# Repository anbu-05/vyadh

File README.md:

# Team Vyadh

This repo consists of all my contributions to Team Vyadh.

## controller

### hardware and code

the controller went through many iterations. 

I had started off working with [NRF24L01](https://github.com/boneman420/vyadh/tree/master/controller/controller%20code/failed%20versions/older%20nrf%20versions) modules for wireless communication. but I could never get two nrf modules to work reliably. even when they did work the range was very bad.

there was a brief moment when i worked with [HC12](https://github.com/boneman420/vyadh/tree/master/controller/controller%20code/failed%20versions/%23hc12%2Besp_now) modules. getting these modules to work was fairly straight forward, but the range, again was not any better.

after both these modules, i decided to try out [LoRa](https://github.com/boneman420/vyadh/tree/master/controller/controller%20code/current%20versions/LoRa%20versions) (specifically the SX1278 module) -and it has been extremely reliable till now. i haven't faced any hiccups with operating the modules nor their range (i get ranges upto 1km with LOS). 

in the LoRa version, ive gone through implementing many features. the electrical subsystem itself consists of 4 main control PCBs as of now (it will be changed out soon) -the [controller](https://github.com/boneman420/vyadh/blob/master/controller/controller%20code/current%20versions/LoRa%20versions/controller_v2_duplex/controller_v2_duplex.ino) (transmitter), [reciever and traversal](https://github.com/boneman420/vyadh/blob/master/controller/controller%20code/current%20versions/LoRa%20versions/traversal_and_reciever_v3_uart_v3_duplex/traversal_and_reciever_v3_uart_v3_duplex.ino), the [robotic arm](https://github.com/boneman420/vyadh/blob/master/controller/controller%20code/current%20versions/LoRa%20versions/robotic_arm_v3_uart_v5/robotic_arm_v3_uart_v5.ino) and [the science kit](https://github.com/boneman420/vyadh/blob/master/controller/controller%20code/current%20versions/LoRa%20versions/science_kit_uart_v2/science_kit_uart_v2.ino) 

.

the controller transmits data, the reciever and traversal board recieves this data, controls the traversal and transmits the same data to the robotic arm and science kit PCBs. 

(i have also implemented duplex communication where the rover sends back telemetry data)

for the communication between these networks the initial plan was to use ESPNow. i tried it out but it creates too much lag between control and robotic arm. so we decided to just use simple serial (UART) connections for now. the future plan is to use a can BUS

### controller PCB

i also wanted to design a decided PCB for the controller. after practicing making an xl4016 buck converter

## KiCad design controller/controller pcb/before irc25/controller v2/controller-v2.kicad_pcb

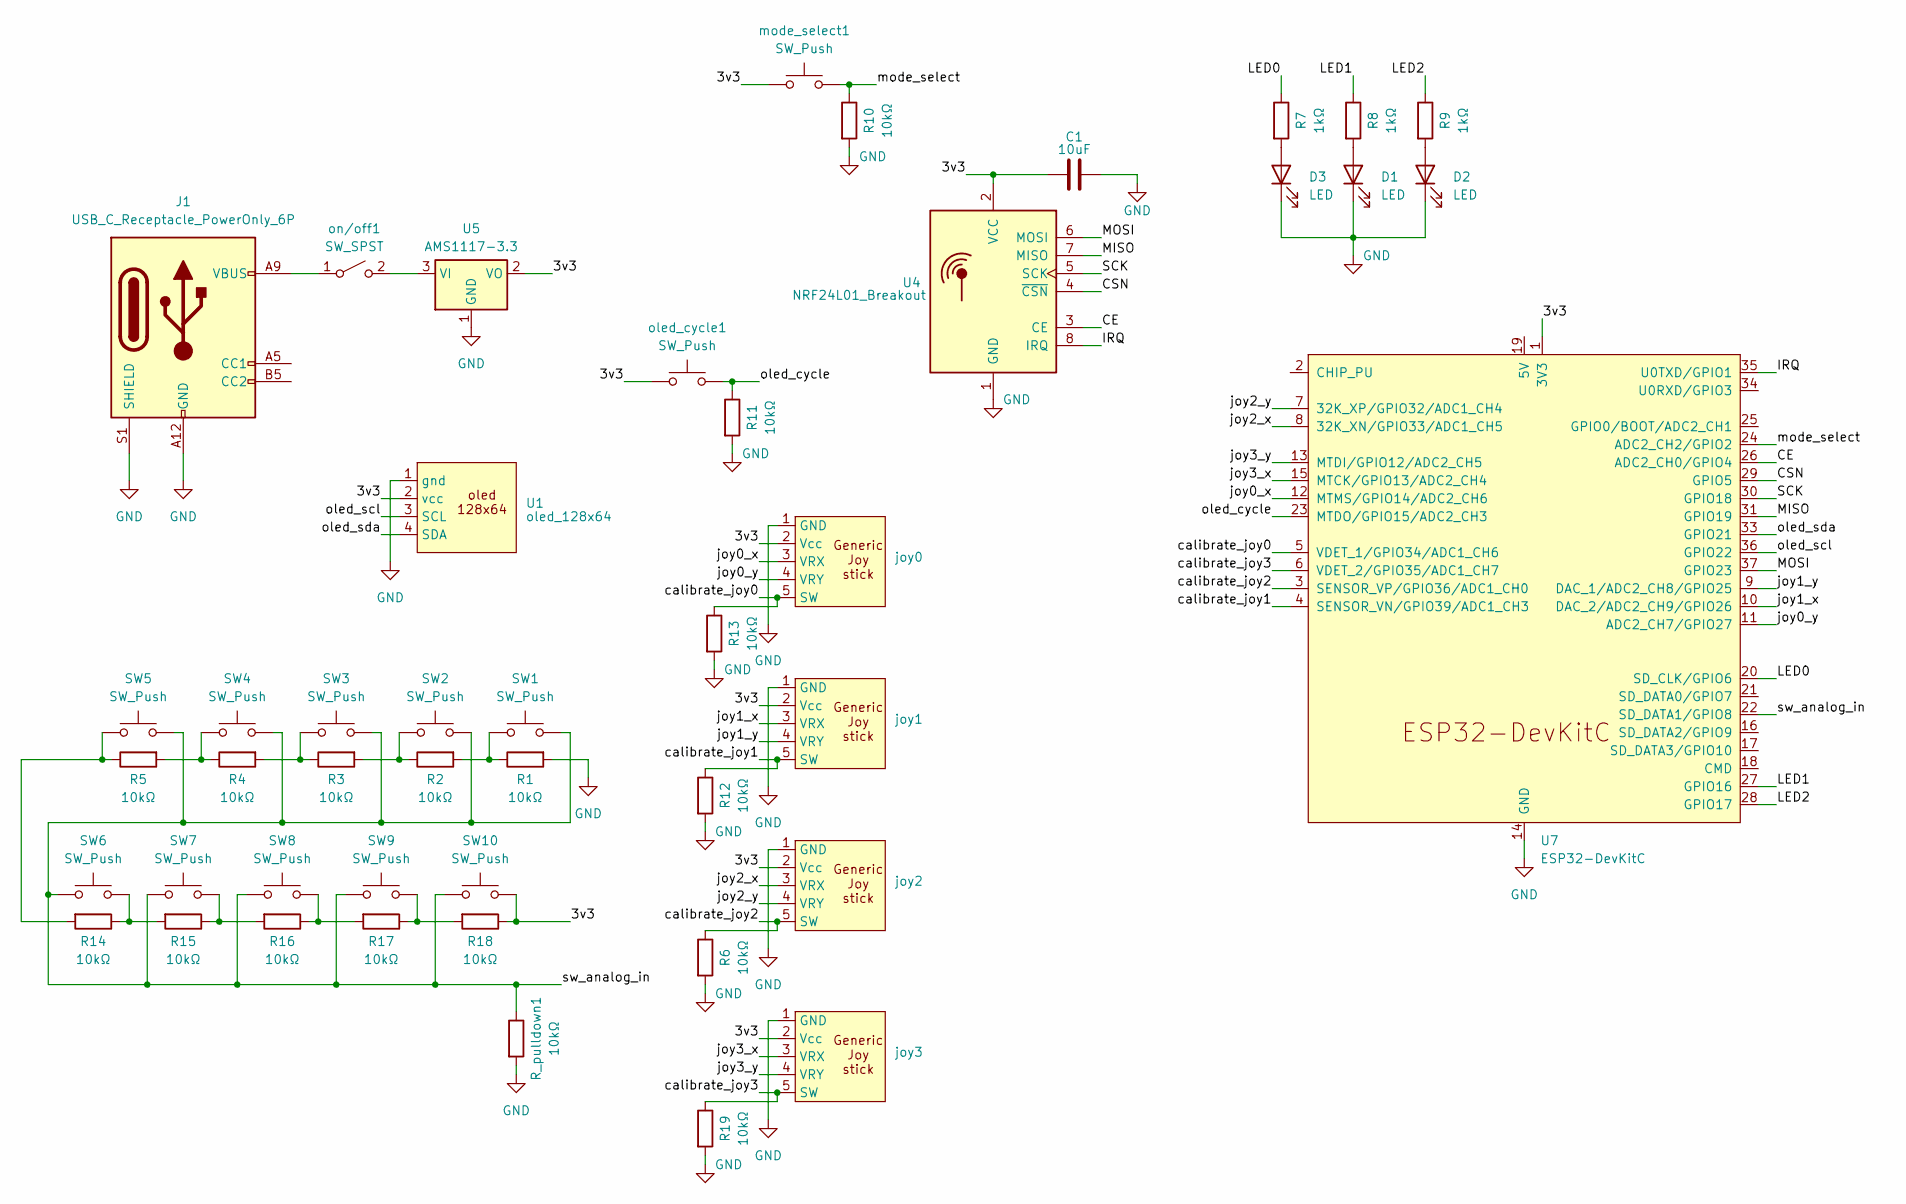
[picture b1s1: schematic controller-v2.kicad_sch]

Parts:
C1: 10uF; C_0603_1608Metric
D1, D2, D3: LED; LED_D3.0mm
J1: USB_C_Receptacle_PowerOnly_6P; USB_C_Receptacle_GCT_USB4125-xx-x_6P_TopMnt_Horizontal
R1, R2, R3, R4, R5, R6, R10, R11, R12, R13, R14, R15, R16, R17, R18, R19: 10kΩ; R_0402_1005Metric
R7, R8, R9: 1kΩ; R_0402_1005Metric
R_pulldown1: 10kΩ; R_0402_1005Metric
SW1, SW2, SW3, SW4, SW5, SW6, SW7, SW8, SW9, SW10: SW_Push; SW_PUSH_6mm
U1: oled_128x64
U4: NRF24L01_Breakout; custom_nrf_controller
U5: AMS1117-3.3; SOT-223-3_TabPin2
U7: ESP32-DevKitC
joy0, joy1, joy2, joy3: generic_joystick_footprint
mode_select1: SW_Push; SW_PUSH_6mm
oled_cycle1: SW_Push; SW_PUSH_6mm
on/off1: SW_SPST; SW_PUSH_1P1T_6x3.5mm_H4.3_APEM_MJTP1243

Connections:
/3v3: C1.1, R18.1, SW10.2, U1.2 (vcc), U4.2 (VCC), U5.2 (VO), U7.1 (3V3), joy0.2 (Vcc), joy1.2 (Vcc), joy2.2 (Vcc), joy3.2 (Vcc), mode_select1.1, oled_cycle1.1
/CE: U4.3 (CE), U7.26 (ADC2_CH0/GPIO4)
/CSN: U4.4 (~CSN), U7.29 (GPIO5)
/IRQ: U4.8 (IRQ), U7.35 (U0TXD/GPIO1)
/LED0: R7.1, U7.20 (SD_CLK/GPIO6)
/LED1: R8.1, U7.27 (GPIO16)
/LED2: R9.1, U7.28 (GPIO17)
/MISO: U4.7 (MISO), U7.31 (GPIO19)
/MOSI: U4.6 (MOSI), U7.37 (GPIO23)
/SCK: U4.5 (SCK), U7.30 (GPIO18)
/calibrate_joy0: R13.1, U7.5 (VDET_1/GPIO34/ADC1_CH6), joy0.5 (SW)
/calibrate_joy1: R12.1, U7.4 (SENSOR_VN/GPIO39/ADC1_CH3), joy1.5 (SW)
/calibrate_joy2: R6.1, U7.3 (SENSOR_VP/GPIO36/ADC1_CH0), joy2.5 (SW)
/calibrate_joy3: R19.1, U7.6 (VDET_2/GPIO35/ADC1_CH7), joy3.5 (SW)
/joy0_x: U7.12 (MTMS/GPIO14/ADC2_CH6), joy0.3 (VRX)
/joy0_y: U7.11 (ADC2_CH7/GPIO27), joy0.4 (VRY)
/joy1_x: U7.10 (DAC_2/ADC2_CH9/GPIO26), joy1.3 (VRX)
/joy1_y: U7.9 (DAC_1/ADC2_CH8/GPIO25), joy1.4 (VRY)
/joy2_x: U7.8 (32K_XN/GPIO33/ADC1_CH5), joy2.3 (VRX)
/joy2_y: U7.7 (32K_XP/GPIO32/ADC1_CH4), joy2.4 (VRY)
/joy3_x: U7.15 (MTCK/GPIO13/ADC2_CH4), joy3.3 (VRX)
/joy3_y: U7.13 (MTDI/GPIO12/ADC2_CH5), joy3.4 (VRY)
/mode_select: R10.1, U7.24 (ADC2_CH2/GPIO2), mode_select1.2
/oled_cycle: R11.1, U7.23 (MTDO/GPIO15/ADC2_CH3), oled_cycle1.2
/oled_scl: U1.3 (SCL), U7.36 (GPIO22)
/oled_sda: U1.4 (SDA), U7.33 (GPIO21)
/sw_analog_in: R_pulldown1.1, SW1.1, SW2.1, SW3.1, SW4.1, SW5.1, SW6.1, SW7.1, SW8.1, SW9.1, SW10.1, U7.22 (SD_DATA1/GPIO8)
GND: C1.2, D1.1 (K), D2.1 (K), D3.1 (K), J1.A12 (GND), J1.B12 (GND), J1.S1 (SHIELD), R1.2, R6.2, R10.2, R11.2, R12.2, R13.2, R19.2, R_pulldown1.2, U1.1 (gnd), U4.1 (GND), U5.1 (GND), U7.14 (GND), U7.32 (GND), U7.38 (GND), joy0.1 (GND), joy1.1 (GND), joy2.1 (GND), joy3.1 (GND)
unnamed: D1.2 (A), R8.2
unnamed: D2.2 (A), R9.2
unnamed: D3.2 (A), R7.2
unnamed: R1.1, R2.2, SW1.2
unnamed: R2.1, R3.2, SW2.2
unnamed: R3.1, R4.2, SW3.2
unnamed: R4.1, R5.2, SW4.2
unnamed: R14.1, R15.2, SW6.2
unnamed: R5.1, R14.2, SW5.2
unnamed: R15.1, R16.2, SW7.2
unnamed: R16.1, R17.2, SW8.2
unnamed: R17.1, R18.2, SW9.2
unnamed: U5.3 (VI), on/off1.2 (B)
unnamed: J1.A9 (VBUS), J1.B9 (VBUS), on/off1.1 (A)

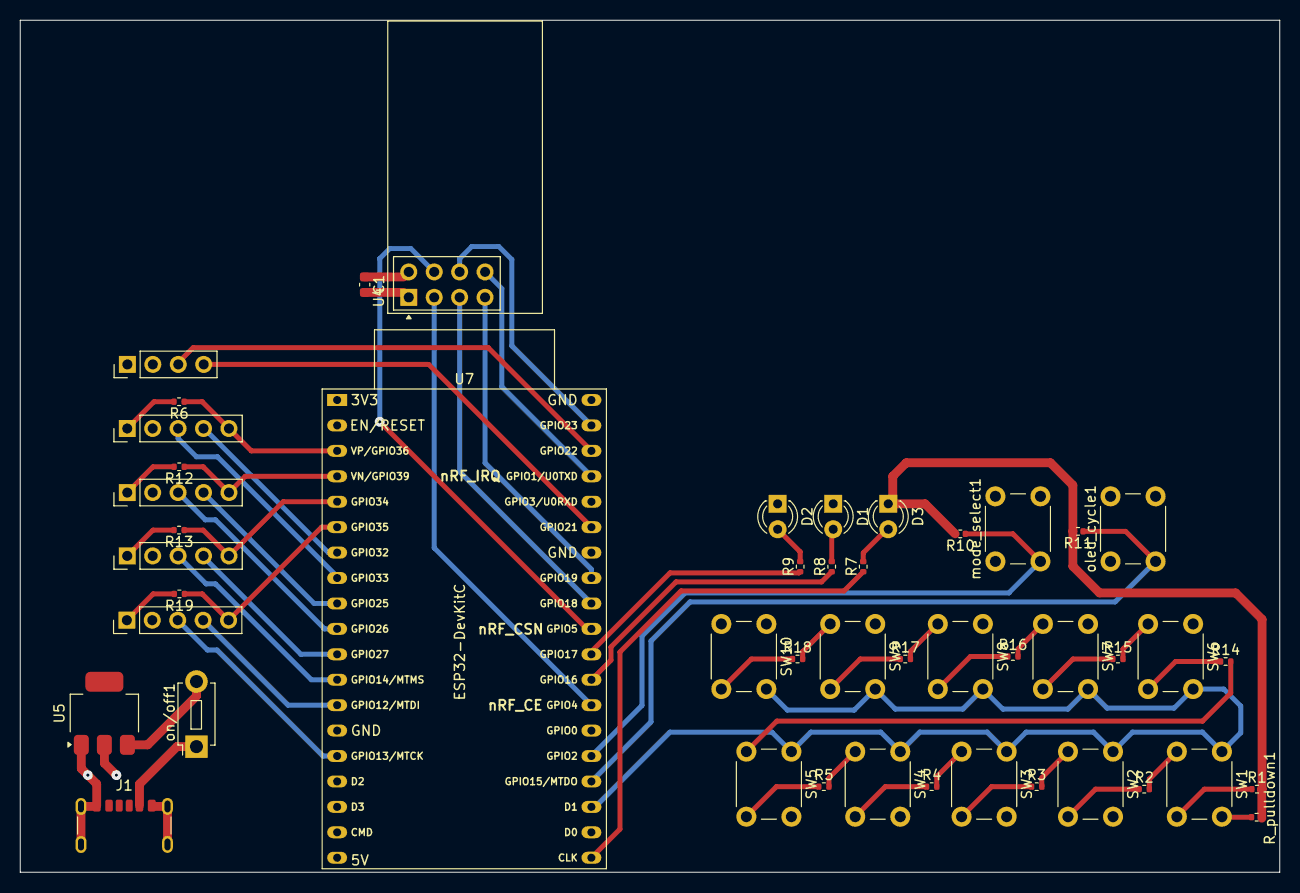
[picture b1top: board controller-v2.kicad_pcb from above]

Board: 4 copper layers, 125.8 x 85.1 mm, 46 parts (0 on the bottom side), 42 nets.

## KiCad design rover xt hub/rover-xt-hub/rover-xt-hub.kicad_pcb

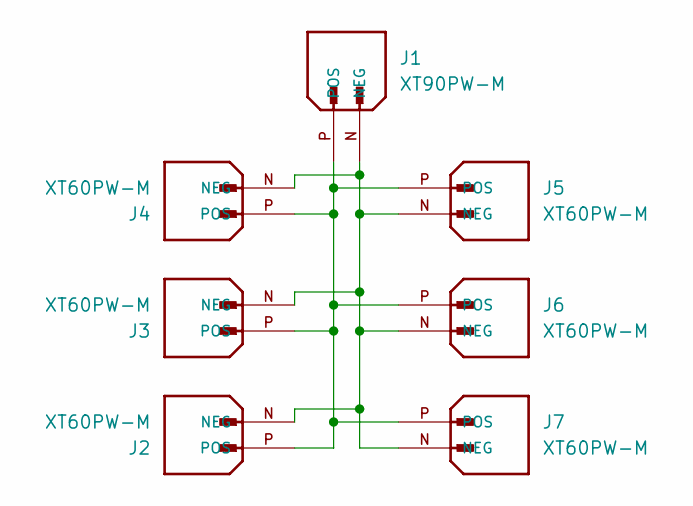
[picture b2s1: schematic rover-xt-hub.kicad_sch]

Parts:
J1: XT90PW-M; AMASS_XT90PW-M; PARTREV V00
J2, J3, J4, J5, J6, J7: XT60PW-M; AMASS_XT60PW-M; PARTREV V1.2

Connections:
unnamed: J1.N (NEG), J2.N (NEG), J3.N (NEG), J4.N (NEG), J5.N (NEG), J6.N (NEG), J7.N (NEG)
unnamed: J1.P (POS), J2.P (POS), J3.P (POS), J4.P (POS), J5.P (POS), J6.P (POS), J7.P (POS)

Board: 2 copper layers, 7 parts (0 on the bottom side), 2 nets, no tracks yet.

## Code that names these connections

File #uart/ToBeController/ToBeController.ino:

//#################################
//#################################

//transmitter code

#include <SPI.h>
#include <nRF24L01.h>
#include <RF24.h>

RF24 radio(4, 5);  // CE, CSN

byte address[6] = "00001";

#define joy1_x 26
#define joy1_y 27
#define but1 13

#define joy2_x 14
#define joy2_y 12
#define but2 25

#define joy3_x 33
#define joy3_y 32
#define but3 35

#define slde1 39
#define slde2 34




void setup() {

  //initializing pins
  // Joystick 1
  pinMode(joy1_x, INPUT);
  pinMode(joy1_y, INPUT);
  pinMode(but1, INPUT);

  // Joystick 2
  pinMode(joy2_x, INPUT);
  pinMode(joy2_y, INPUT);
  pinMode(but2, INPUT);

  //joystick 3
  pinMode(joy3_x, INPUT);
  pinMode(joy3_y, INPUT);
  pinMode(but3, INPUT);

  //slide switches
  pinMode(slde1, INPUT);
  pinMode(slde2, INPUT);

  // begining the module/library
  if (!radio.begin()) {
  Serial.println(F("radio hardware not responding!"));
  while (1) {} // hold program in infinite loop to prevent subsequent errors
  }

  Serial.begin(115200);
  Serial.println("start");

  //the RF module's power level:
  //Options: RF24_PA_MIN, RF24_PA_LOW, RF24_PA_HIGH, RF24_PA_MAX
  radio.setPALevel(RF24_PA_MAX);

  //setting this RF module to transmit mode:
  radio.stopListening();

  // Open the writing pipe with the defined address
  // This is the address the data will be sent to
  // use a different address if you wanna send the data to a different module.
  radio.openWritingPipe(address);

}

struct controllerData{
  int joystick1_x;
  int joystick1_y;
  int Button1;

  int joystick2_x;
  int joystick2_y;
  int Button2;

  int joystick3_x;
  int joystick3_y;
  int Button3;

  int slide1;
  int slide2;
};

controllerData payload;

void loop() {

  // Joystick 1
  payload.joystick1_x = analogRead(joy1_x);
  payload.joystick1_y = analogRead(joy1_y);
  payload.Button1 = digitalRead(but1);

  // Joystick 2
  payload.joystick2_x = analogRead(joy2_x);
  payload.joystick2_y = analogRead(joy2_y);
  payload.Button2 = digitalRead(but2);

  //joystick 3
  payload.joystick3_x = analogRead(joy3_x);
  payload.joystick3_y = analogRead(joy3_y);
  payload.Button3 = digitalRead(but3);

  payload.slide1 = digitalRead(slde1);
  payload.slide2 = digitalRead(slde2);


  Serial.print(payload.joystick1_x);
  Serial.print(",");
  Serial.print(payload.joystick1_y);
  Serial.print(",");
  Serial.print(payload.Button1);
  Serial.println("  ");

  Serial.print(payload.joystick2_x);
  Serial.print(",");
  Serial.print(payload.joystick2_y);
  Serial.print(",");
  Serial.print(payload.Button2);
  Serial.println("  ");

  Serial.print(payload.joystick3_x);
  Serial.print(",");
  Serial.print(payload.joystick3_y);
  Serial.print(",");
  Serial.print(payload.Button3);
  Serial.println("  ");

  Serial.print(payload.slide1);
  Serial.print(",");
  Serial.print(payload.slide2);
  Serial.println("  ");

  Serial.println("  ");
  Serial.println("  ");
  Serial.println("  ");

  radio.write(&payload, sizeof(payload));

  delay(20);
}

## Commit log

2024-11-08 added README file
2024-11-08 edited readme file
2024-11-10 3 joysticks, reciever+traversal, robotic arm
2024-11-10 final goal for the controller
2024-11-11 robotic arm works with esp now
2024-11-14 updated esp now part of the code
2024-11-14 restructured the repo
2024-11-15 working on sending multiple packets
2024-12-01 added the controller pcb and xt-hub pcb
2024-12-01 restructured the directory
2024-12-01 no changes
2024-12-04 changes to radio.available(), found out a way to reproduce the instability
2025-01-10 reinstalled git
2025-01-11 small change in traversal code
2025-01-12 robotic arm works (without gripper)
2025-01-13 exchanged rst and dpio0
2025-01-15 changed pin numbers for joysticks
2025-01-15 robotic arm code with positions
2025-01-16 robotic arm code with toggle and wrist
2025-01-16 jittering problem due to esp now, need to look for change
2025-01-17 changes to gradual increase and robotic arm code
2025-01-17 uart instead of espNOW
2025-01-18 uart working reliably
2025-01-18 added science kit button
2025-01-18 added gripper control
2025-01-18 need to figure out gradual increase
2025-01-21 added simple gradual increase
2025-01-21 fixed toggle problem and implemented science kit code
2025-01-21 name change
2025-01-26 controller v2, traversal v3.2, robotic arm v3.4
2025-01-28 controller v2, trav v3.3, robarm v3.5
2025-01-31 controller v2, traversal v3.3, robarm v3.5
2025-02-11 controller v2, traversal v3.3, robarm v3.5
2025-03-10 commit after 1 month
2025-03-10 lora duplex works
2025-03-11 duplex code improvements
2025-04-27 updating the readme file
2025-04-27 pics
2025-04-27 more pics
2025-05-10 made reciever PCB
2025-06-05 (auto)
2025-08-11 commit after a long time, refer to individual repos
